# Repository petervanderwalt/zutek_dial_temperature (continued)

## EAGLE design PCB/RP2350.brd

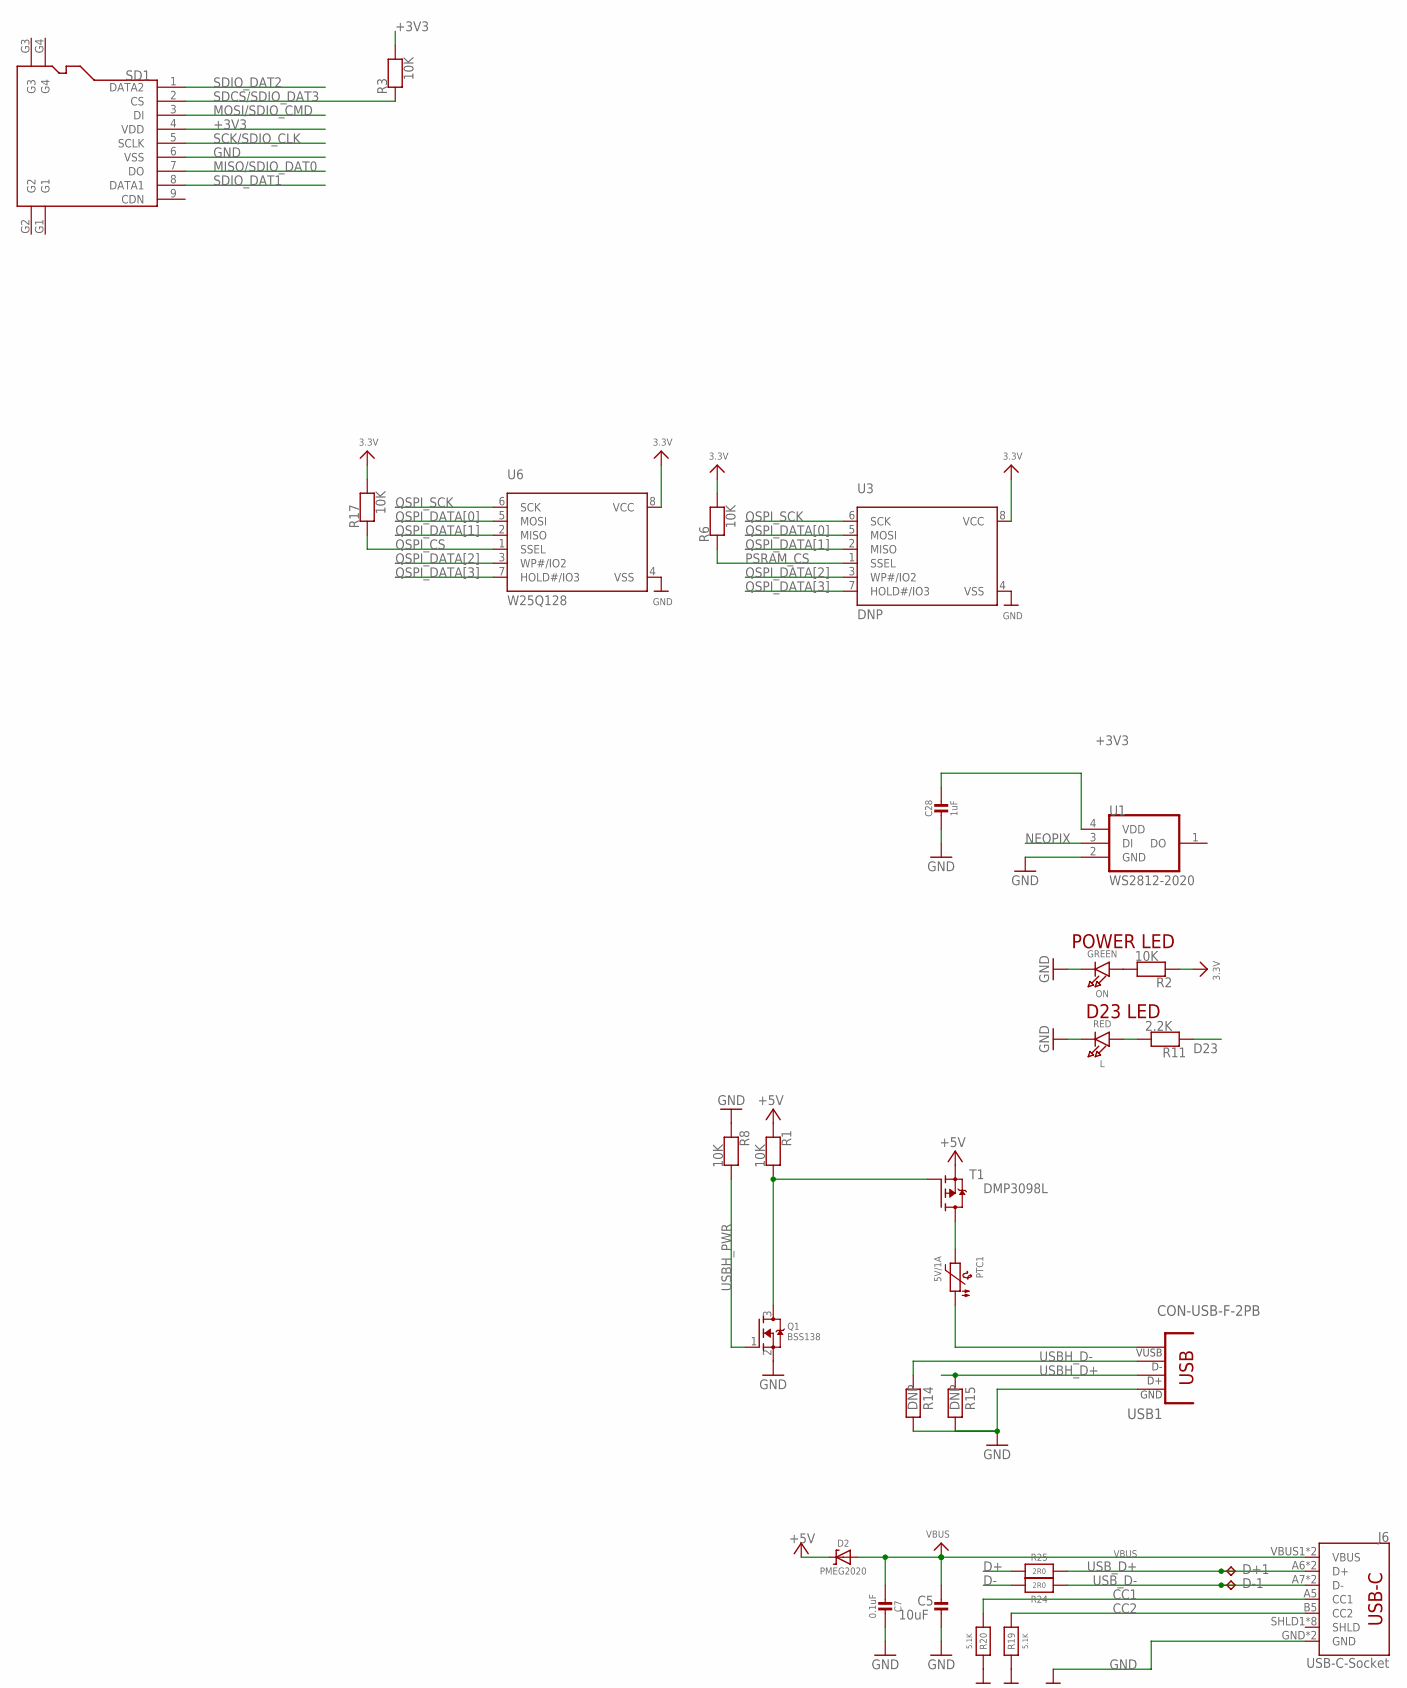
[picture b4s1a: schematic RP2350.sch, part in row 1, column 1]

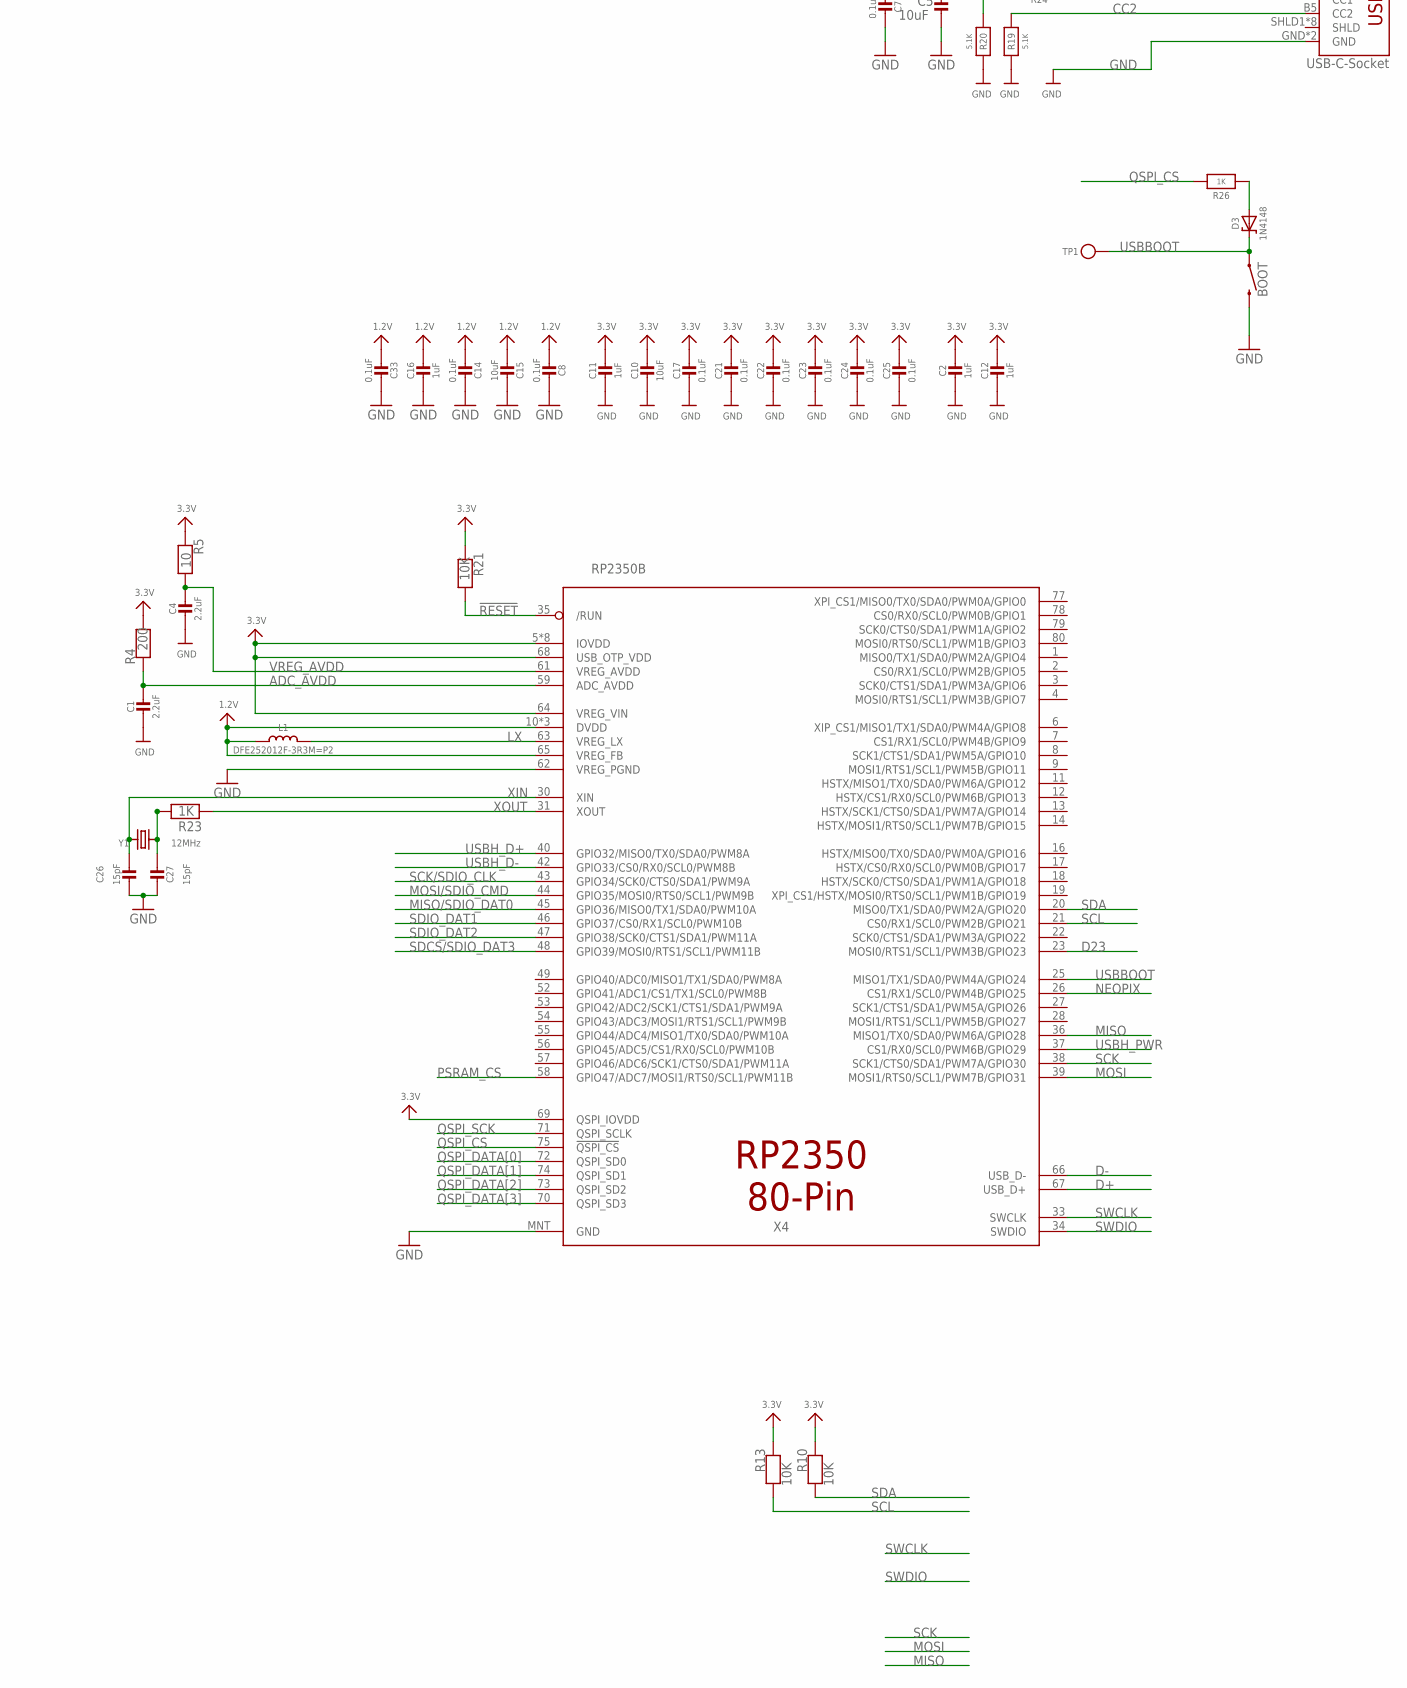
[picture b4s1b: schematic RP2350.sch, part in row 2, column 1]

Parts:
BOOT: MOMENTARY-SWITCH-SPST-SMD-6.0X3.5MM; TACTILE_SWITCH_SMD_6.0X3.5MM
C1, C4: 2.2uF; 0603-NO
C2, C11, C12, C16, C28: 1uF; 0603-NO
C5: 10uF; 0805-NO
C7, C8, C14, C17, C21, C22, C23, C24, C25, C33: 0.1uF; 0603-NO
C10, C15: 10uF; 0603-NO_WIDE
C26, C27: 15pF; 0603-NO
D2: PMEG2020; SOD-323
D3: 1N4148; SOD-323
D+1: TPB1,27; B1,27
D-1: TPB1,27; B1,27
J6: USB-C-Socket; USB-C-16P
L: RED; CHIPLED_0603_NOOUTLINE
L1: DFE252012F-3R3M=P2; INDUCTOR_1007
ON: GREEN; CHIPLED_0603_NOOUTLINE
PTC1: 5V/1A; 0805-NO
Q1: BSS138; SOT23-WIDE
R1, R2, R3, R6, R8, R10, R13, R17, R21: 10K; 0603-NO
R4: 200; 0603-NO
R5: 10; 0603-NO
R11: 2.2K; 0603-NO
R14, R15: DNP; 0603-NO
R19, R20: 5.1K; 0603-NO
R23, R26: 1K; 0603-NO
R24, R25: 2R0; 0603-NO
SD1: HOLDER-MICROSD-9P; 9P-SMD-W/-RING
T1: DMP3098L; SOT23-WIDE
TP1: TESTPOINTROUND1.5MMNO; TESTPOINT_ROUND_1.5MM_NO
U1: WS2812-2020; LED_WS2812-2020
U3: DNP; SOIC8_208MIL
U6: W25Q128; SOIC8_208MIL
USB1: CON-USB-F-2PB; CONN_USB_A_F
X4: RP2350B; QFN80
Y1: 12MHz; CRYSTAL_2.5X2

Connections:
1.2V: C8.2, C14.2, C15.2, C16.1, C33.2, L1.P$1 (1), X4.10 (DVDD), X4.32 (DVDD), X4.51 (DVDD), X4.65 (VREG_FB)
!RESET: R21.2, X4.35 (/RUN)
+3V3: C2.1, C10.1, C11.1, C12.1, C17.1, C21.1, C22.1, C23.1, C24.1, C25.1, C28.1, R2.1, R3.2, R4.2, R5.1, R6.2, R10.1, R13.1, R17.2, R21.1, SD1.4 (VDD), U1.4 (VDD), U3.8 (VCC), U6.8 (VCC), X4.5 (IOVDD), X4.15 (IOVDD), X4.24 (IOVDD), X4.29 (IOVDD), X4.41 (IOVDD), X4.50 (IOVDD), X4.60 (IOVDD), X4.64 (VREG_VIN), X4.68 (USB_OTP_VDD), X4.69 (QSPI_IOVDD), X4.76 (IOVDD)
+5V: D2.C, R1.1, T1.2 (S)
ADC_AVDD: C1.1, R4.1, X4.59 (ADC_AVDD)
CC1: J6.A5 (CC1), R20.2
CC2: J6.B5 (CC2), R19.2
D23: R11.1, X4.23 (MOSI0/RTS1/SCL1/PWM3B/GPIO23)
D+: R25.2, X4.67 (USB_D+)
D-: R24.2, X4.66 (USB_D-)
GND: BOOT.2, C1.2, C2.2, C4.2, C5.1, C7.2, C8.1, C10.2, C11.2, C12.2, C14.1, C15.1, C16.2, C17.2, C21.2, C22.2, C23.2, C24.2, C25.2, C26.1, C27.1, C28.2, C33.1, J6.GND, J6.GND2 (GND), L.C, ON.C, Q1.2 (S), R8.1, R14.1, R15.1, R19.1, R20.1, SD1.6 (VSS), U1.2 (GND), U3.4 (VSS), U6.4 (VSS), USB1.4 (GND), X4.62 (VREG_PGND), X4.MNT (GND)
LX: L1.P$2 (2), X4.63 (VREG_LX)
MISO: X4.36 (MISO1/TX0/SDA0/PWM6A/GPIO28)
MISO/SDIO_DAT0: SD1.7 (DO), X4.45 (GPIO36/MISO0/TX1/SDA0/PWM10A)
MOSI: X4.39 (MOSI1/RTS0/SCL1/PWM7B/GPIO31)
MOSI/SDIO_CMD: SD1.3 (DI), X4.44 (GPIO35/MOSI0/RTS0/SCL1/PWM9B)
unnamed: L.A, R11.2
unnamed: ON.A, R2.2
unnamed: PTC1.1, USB1.1 (VUSB)
unnamed: PTC1.2, T1.3 (D)
unnamed: Q1.3 (D), R1.2, T1.1 (G)
unnamed: D3.A, R26.2
unnamed: C27.2, R23.1, Y1.3 (2)
NEOPIX: U1.3 (DI), X4.26 (CS1/RX1/SCL0/PWM4B/GPIO25)
PSRAM_CS: R6.1, U3.1 (SSEL), X4.58 (GPIO47/ADC7/MOSI1/RTS0/SCL1/PWM11B)
QSPI_CS: R17.1, R26.1, U6.1 (SSEL), X4.75 (!QSPI_CS)
QSPI_DATA[0]: U3.5 (MOSI), U6.5 (MOSI), X4.72 (QSPI_SD0)
QSPI_DATA[1]: U3.2 (MISO), U6.2 (MISO), X4.74 (QSPI_SD1)
QSPI_DATA[2]: U3.3 (WP#/IO2), U6.3 (WP#/IO2), X4.73 (QSPI_SD2)
QSPI_DATA[3]: U3.7 (HOLD#/IO3), U6.7 (HOLD#/IO3), X4.70 (QSPI_SD3)
QSPI_SCK: U3.6 (SCK), U6.6 (SCK), X4.71 (QSPI_SCLK)
SCK: X4.38 (SCK1/CTS0/SDA1/PWM7A/GPIO30)
SCK/SDIO_CLK: SD1.5 (SCLK), X4.43 (GPIO34/SCK0/CTS0/SDA1/PWM9A)
SCL: R13.2, X4.21 (CS0/RX1/SCL0/PWM2B/GPIO21)
SDA: R10.2, X4.20 (MISO0/TX1/SDA0/PWM2A/GPIO20)
SDCS/SDIO_DAT3: R3.1, SD1.2 (CS), X4.48 (GPIO39/MOSI0/RTS1/SCL1/PWM11B)
SDIO_DAT1: SD1.8 (DATA1), X4.46 (GPIO37/CS0/RX1/SCL0/PWM10B)
SDIO_DAT2: SD1.1 (DATA2), X4.47 (GPIO38/SCK0/CTS1/SDA1/PWM11A)
SWCLK: X4.33 (SWCLK)
SWDIO: X4.34 (SWDIO)
USBBOOT: BOOT.1, D3.C, TP1.P$1, X4.25 (MISO1/TX1/SDA0/PWM4A/GPIO24)
USBH_D+: R15.2, USB1.3 (D+), X4.40 (GPIO32/MISO0/TX0/SDA0/PWM8A)
USBH_D-: R14.2, USB1.2 (D-), X4.42 (GPIO33/CS0/RX0/SCL0/PWM8B)
USBH_PWR: Q1.1 (G), R8.2, X4.37 (CS1/RX0/SCL0/PWM6B/GPIO29)
USB_D+: D+1.TP, J6.A6 (D+), J6.B6 (D+), R25.1
USB_D-: D-1.TP, J6.A7 (D-), J6.B7 (D-), R24.1
VBUS: C5.2, C7.1, D2.A, J6.VBUS1 (VBUS), J6.VBUS2 (VBUS)
VREG_AVDD: C4.1, R5.2, X4.61 (VREG_AVDD)
XIN: C26.2, X4.30 (XIN), Y1.1
XOUT: R23.2, X4.31 (XOUT)

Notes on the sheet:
POWER LED
D23 LED

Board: 2 copper layers, 62 parts (0 on the bottom side), 45 nets, no tracks yet.

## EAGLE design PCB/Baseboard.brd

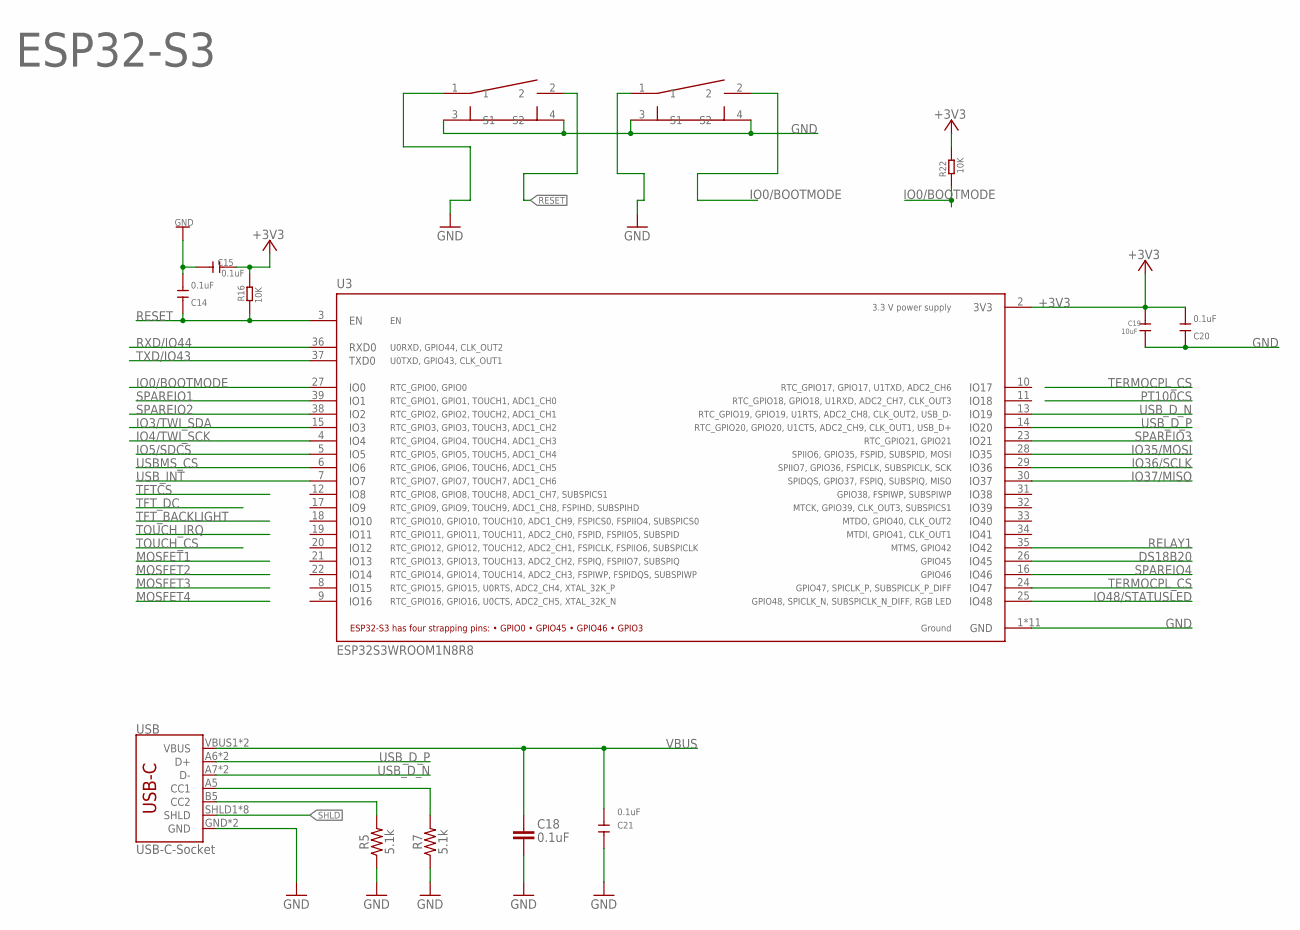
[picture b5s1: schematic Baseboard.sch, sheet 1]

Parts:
C14, C15, C20, C21: 0.1uF; DISCRETE_C0603
C18: 0.1uF; 0603-CAP
C19: 10uF; C1206
MODE: RIGHTANGLETACTILE; DP_DEVICES_SW_TACT_STANDARD_RIGHT_ANGLE
R5, R7: 5.1k; 0603@1
R16, R22: 10K; R0603
RESET: RIGHTANGLETACTILE; DP_DEVICES_SW_TACT_STANDARD_RIGHT_ANGLE
U3: ESP32S3WROOM1N8R8; XCVR_ESP32S3WROOM1N8R8
USB: USB-C-Socket; USB-C-16P

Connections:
+3V3: C15.1, C19.1, C20.2, R16.2, R22.2, U3.2 (3V3); also elsewhere on the board
CC1: R7.2, USB.A5 (CC1)
CC2: R5.2, USB.B5 (CC2)
DS18B20: U3.26 (IO45); also elsewhere on the board
GND: C14.2, C15.2, C18.2, C19.2, C20.1, C21.1, MODE.1, MODE.3 (S1), MODE.4 (S2), R5.1, R7.1, RESET.1, RESET.3 (S1), RESET.4 (S2), U3.1 (GND), U3.40 (GND), U3.41_1 (GND), U3.41_2 (GND), U3.41_3 (GND), U3.41_4 (GND), U3.41_5 (GND), U3.41_6 (GND), U3.41_7 (GND), U3.41_8 (GND), U3.41_9 (GND), USB.GND, USB.GND2 (GND); also elsewhere on the board
IO0/BOOTMODE: MODE.2, R22.1, U3.27 (IO0)
IO3/TWI_SDA: U3.15 (IO3); also elsewhere on the board
IO4/TWI_SCK: U3.4 (IO4); also elsewhere on the board
IO5/SDCS: U3.5 (IO5); also elsewhere on the board
IO35/MOSI: U3.28 (IO35); also elsewhere on the board
IO36/SCLK: U3.29 (IO36); also elsewhere on the board
IO37/MISO: U3.30 (IO37); also elsewhere on the board
IO48/STATUSLED: U3.25 (IO48); also elsewhere on the board
RELAY1: U3.35 (IO42); also elsewhere on the board
RESET: C14.1, R16.1, RESET.2, U3.3 (EN)
RXD/IO44: U3.36 (RXD0); also elsewhere on the board
SHLD: USB.SHLD1 (SHLD), USB.SHLD2 (SHLD), USB.SHLD3 (SHLD), USB.SHLD4 (SHLD), USB.SHLD5 (SHLD), USB.SHLD6 (SHLD), USB.SHLD7 (SHLD), USB.SHLD8 (SHLD)
SPAREIO1: U3.39 (IO1); also elsewhere on the board
SPAREIO2: U3.38 (IO2); also elsewhere on the board
SPAREIO3: U3.23 (IO21); also elsewhere on the board
SPAREIO4: U3.16 (IO46); also elsewhere on the board
TERMOCPL_CS: U3.24 (IO47); also elsewhere on the board
TXD/IO43: U3.37 (TXD0); also elsewhere on the board
USBMS_CS: U3.6 (IO6); also elsewhere on the board
USB_D_N: U3.13 (IO19), USB.A7 (D-), USB.B7 (D-)
USB_D_P: U3.14 (IO20), USB.A6 (D+), USB.B6 (D+)
USB_INT: U3.7 (IO7); also elsewhere on the board
VBUS: C18.1, C21.2, USB.VBUS1 (VBUS), USB.VBUS2 (VBUS); also elsewhere on the board

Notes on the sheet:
ESP32-S3

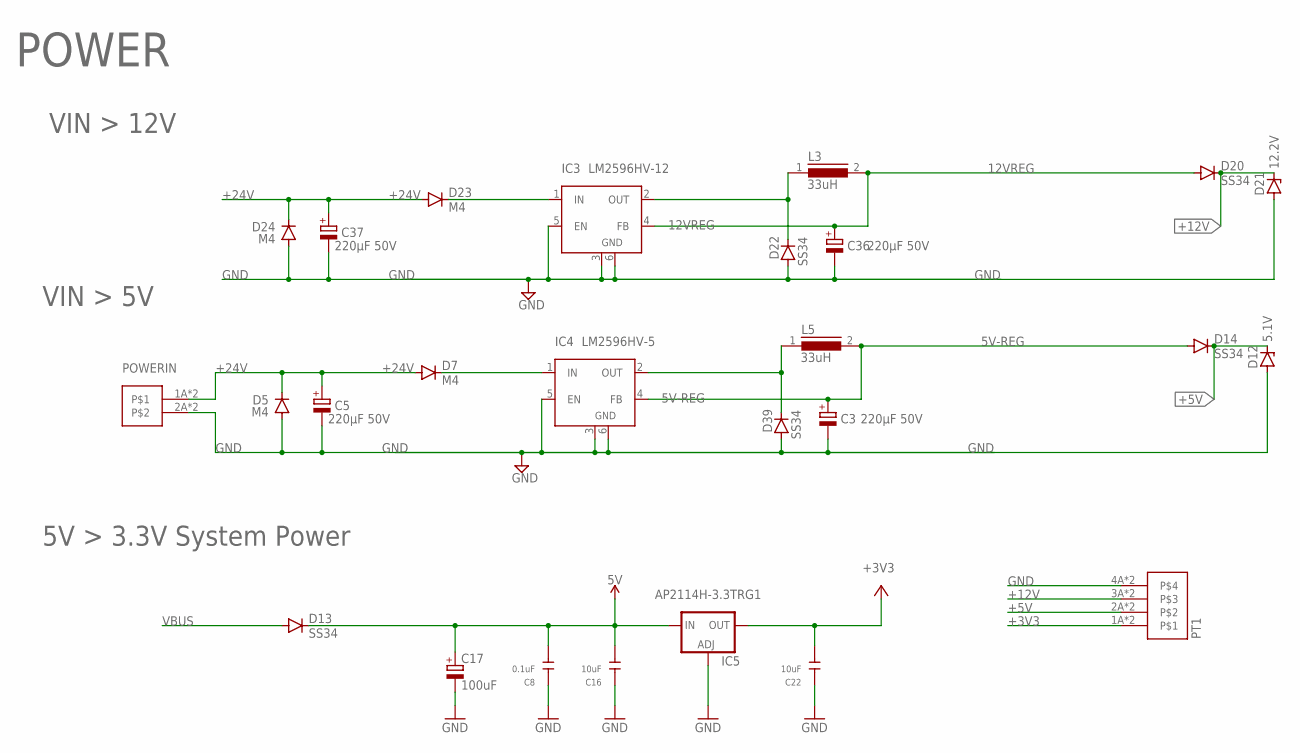
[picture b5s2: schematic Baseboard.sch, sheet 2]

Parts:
C3, C5, C36, C37: 220µF 50V; PANASONIC_E
C8: 0.1uF; DISCRETE_C0603
C16, C22: 10uF; C1206
C17: 100uF; PANASONIC_D
D5, D7, D23, D24: M4; DO-214AC
D12: 5.1V; SMB
D13, D14, D20: SS34; DO-214AC
D21: 12.2V; SMB
D22, D39: SS34; SOD87
IC3: LM2596HV-12; TO263-5
IC4: LM2596HV-5; TO263-5
IC5: AP2114H-3.3TRG1; SOT223
L3, L5: 33uH; DR127
POWERIN: WJ212R-THR-3.5-2
PT1: WJ212R-THR-3.5-4

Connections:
5V-REG: C3.+, D14.A, IC4.4 (FB), L5.2
12VREG: C36.+, D20.A, IC3.4 (FB), L3.2
+3V3: C22.1, IC5.4 (OUT), PT1.1A, PT1.1B; also elsewhere on the board
+5V: C8.2, C16.1, C17.+, D12.C, D13.C, D14.C, IC5.3 (IN), PT1.2A, PT1.2B; also elsewhere on the board
+12V: D20.C, D21.C, PT1.3A, PT1.3B
+24V: C5.+, C37.+, D5.C, D7.A, D23.A, D24.C, POWERIN.1A, POWERIN.1B; also elsewhere on the board
+24V1: D7.C, IC4.1 (IN)
+24V2: D23.C, IC3.1 (IN)
GND: C3.-, C5.-, C8.1, C16.2, C17.-, C22.2, C36.-, C37.-, D5.A, D12.A, D21.A, D22.2 (A), D24.A, D39.2 (A), IC3.3 (GND), IC3.5 (EN), IC3.6 (GND), IC4.3 (GND), IC4.5 (EN), IC4.6 (GND), IC5.1 (ADJ), POWERIN.2A, POWERIN.2B, PT1.4A, PT1.4B; also elsewhere on the board
unnamed: D22.1 (C), IC3.2 (OUT), L3.1
unnamed: D39.1 (C), IC4.2 (OUT), L5.1
VBUS: D13.A; also elsewhere on the board

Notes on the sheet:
5V > 3.3V System Power
POWER
VIN > 5V
VIN > 12V

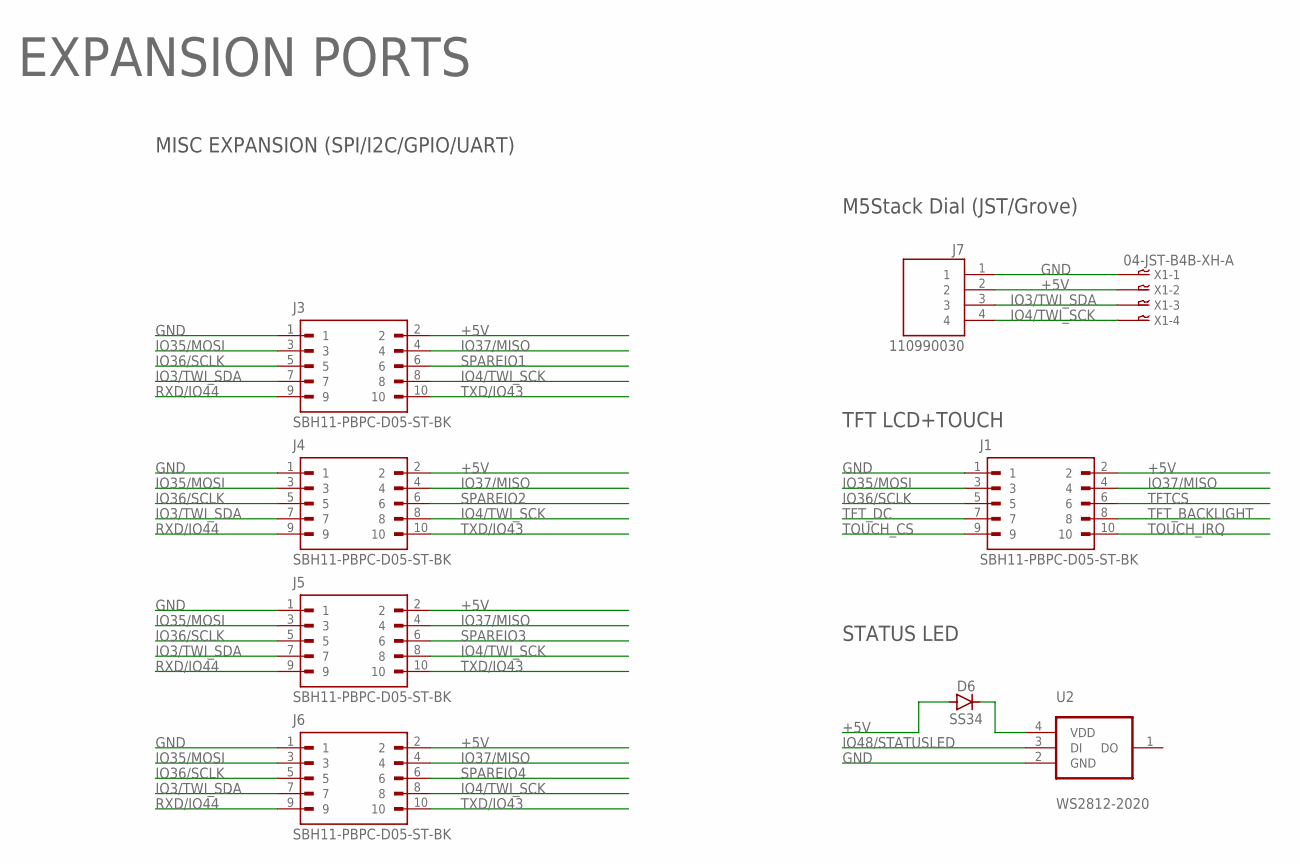
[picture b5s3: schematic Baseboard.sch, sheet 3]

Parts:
D6: SS34; SOD87
J1, J3, J4, J5, J6: SBH11-PBPC-D05-ST-BK; SULLINS_SBH11-PBPC-D05-ST-BK
J7: 110990030; SEEED_110990030
U2: WS2812-2020; LED_WS2812-2020
X1: 04-JST-B4B-XH-A; B4B-XH

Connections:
+5V: D6.2 (A), J1.2, J3.2, J4.2, J5.2, J6.2, J7.2, X1.P$2; also elsewhere on the board
GND: J1.1, J3.1, J4.1, J5.1, J6.1, J7.1, U2.2 (GND), X1.P$1; also elsewhere on the board
IO3/TWI_SDA: J3.7, J4.7, J5.7, J6.7, J7.3, X1.P$3; also elsewhere on the board
IO4/TWI_SCK: J3.8, J4.8, J5.8, J6.8, J7.4, X1.P$4; also elsewhere on the board
IO35/MOSI: J1.3, J3.3, J4.3, J5.3, J6.3; also elsewhere on the board
IO36/SCLK: J1.5, J3.5, J4.5, J5.5, J6.5; also elsewhere on the board
IO37/MISO: J1.4, J3.4, J4.4, J5.4, J6.4; also elsewhere on the board
IO48/STATUSLED: U2.3 (DI); also elsewhere on the board
unnamed: D6.1 (C), U2.4 (VDD)
RXD/IO44: J3.9, J4.9, J5.9, J6.9; also elsewhere on the board
SPAREIO1: J3.6; also elsewhere on the board
SPAREIO2: J4.6; also elsewhere on the board
SPAREIO3: J5.6; also elsewhere on the board
SPAREIO4: J6.6; also elsewhere on the board
TFTCS: J1.6
TFT_BACKLIGHT: J1.8
TFT_DC: J1.7
TOUCH_CS: J1.9
TOUCH_IRQ: J1.10
TXD/IO43: J3.10, J4.10, J5.10, J6.10; also elsewhere on the board

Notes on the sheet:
M5Stack Dial (JST/Grove)
TFT LCD+TOUCH
MISC EXPANSION (SPI/I2C/GPIO/UART)
EXPANSION PORTS
STATUS LED

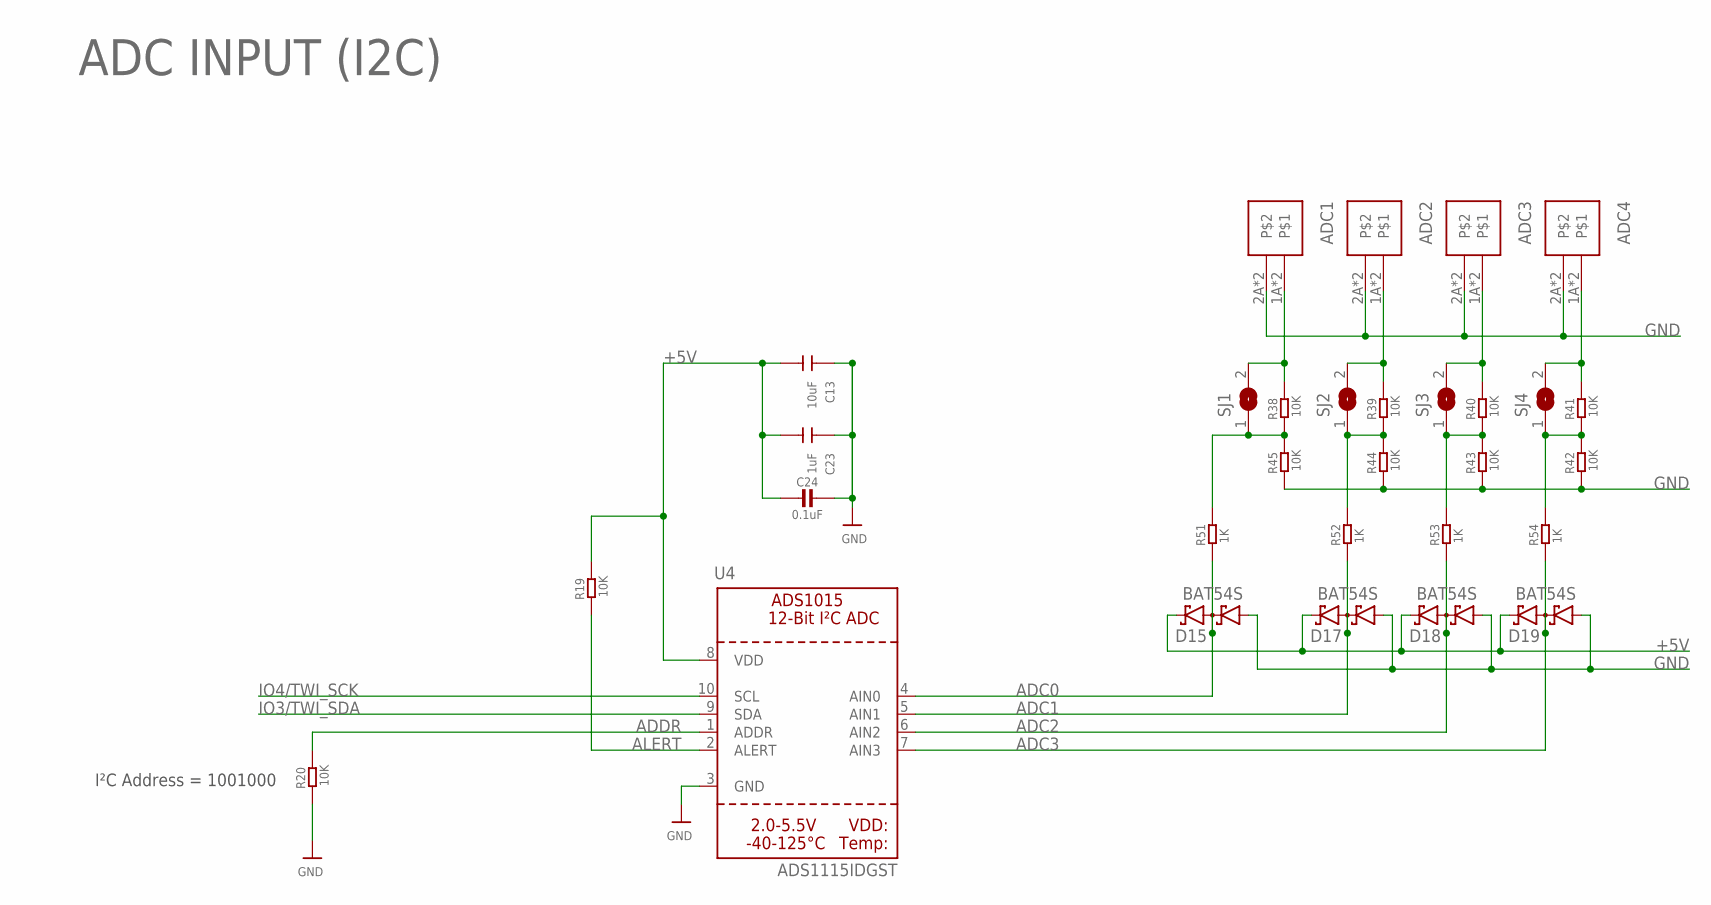
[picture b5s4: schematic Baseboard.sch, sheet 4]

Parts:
ADC1, ADC2, ADC3, ADC4: WJ212R-THR-3.5-2
C13: 10uF; C1206
C23: 1uF; C1206
C24: 0.1uF; 0805-NO
D15, D17, D18, D19: BAT54S; SOT23
R19, R20: 10K; R0603
R38, R39, R40, R41, R42, R43, R44, R45: 10K; R0204/5
R51, R52, R53, R54: 1K; R0204/5
SJ1, SJ2, SJ3, SJ4: SJ
U4: ADS1115IDGST; MSOP10

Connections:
+5V: C13.1, C23.1, C24.2, D15.2 (C2), D17.2 (C2), D18.2 (C2), D19.2 (C2), R19.1, U4.8 (VDD); also elsewhere on the board
ADC0: D15.3 (C1A2), R51.2, U4.4 (AIN0)
ADC1: D17.3 (C1A2), R52.2, U4.5 (AIN1)
ADC2: D18.3 (C1A2), R53.2, U4.6 (AIN2)
ADC3: D19.3 (C1A2), R54.2, U4.7 (AIN3)
ADDR: R20.1, U4.1 (ADDR); also elsewhere on the board
ALERT: R19.2, U4.2 (ALERT); also elsewhere on the board
GND: ADC1.2A, ADC1.2B, ADC2.2A, ADC2.2B, ADC3.2A, ADC3.2B, ADC4.2A, ADC4.2B, C13.2, C23.2, C24.1, D15.1 (A1), D17.1 (A1), D18.1 (A1), D19.1 (A1), R20.2, R42.2, R43.2, R44.2, R45.2, U4.3 (GND); also elsewhere on the board
IO3/TWI_SDA: U4.9 (SDA); also elsewhere on the board
IO4/TWI_SCK: U4.10 (SCL); also elsewhere on the board
unnamed: ADC1.1A, ADC1.1B, R38.1, SJ1.2
unnamed: ADC2.1A, ADC2.1B, R39.1, SJ2.2
unnamed: ADC3.1A, ADC3.1B, R40.1, SJ3.2
unnamed: ADC4.1A, ADC4.1B, R41.1, SJ4.2
unnamed: R38.2, R45.1, R51.1, SJ1.1
unnamed: R39.2, R44.1, R52.1, SJ2.1
unnamed: R40.2, R43.1, R53.1, SJ3.1
unnamed: R41.2, R42.1, R54.1, SJ4.1

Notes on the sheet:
I²C Address = 1001000
ADC INPUT (I2C)

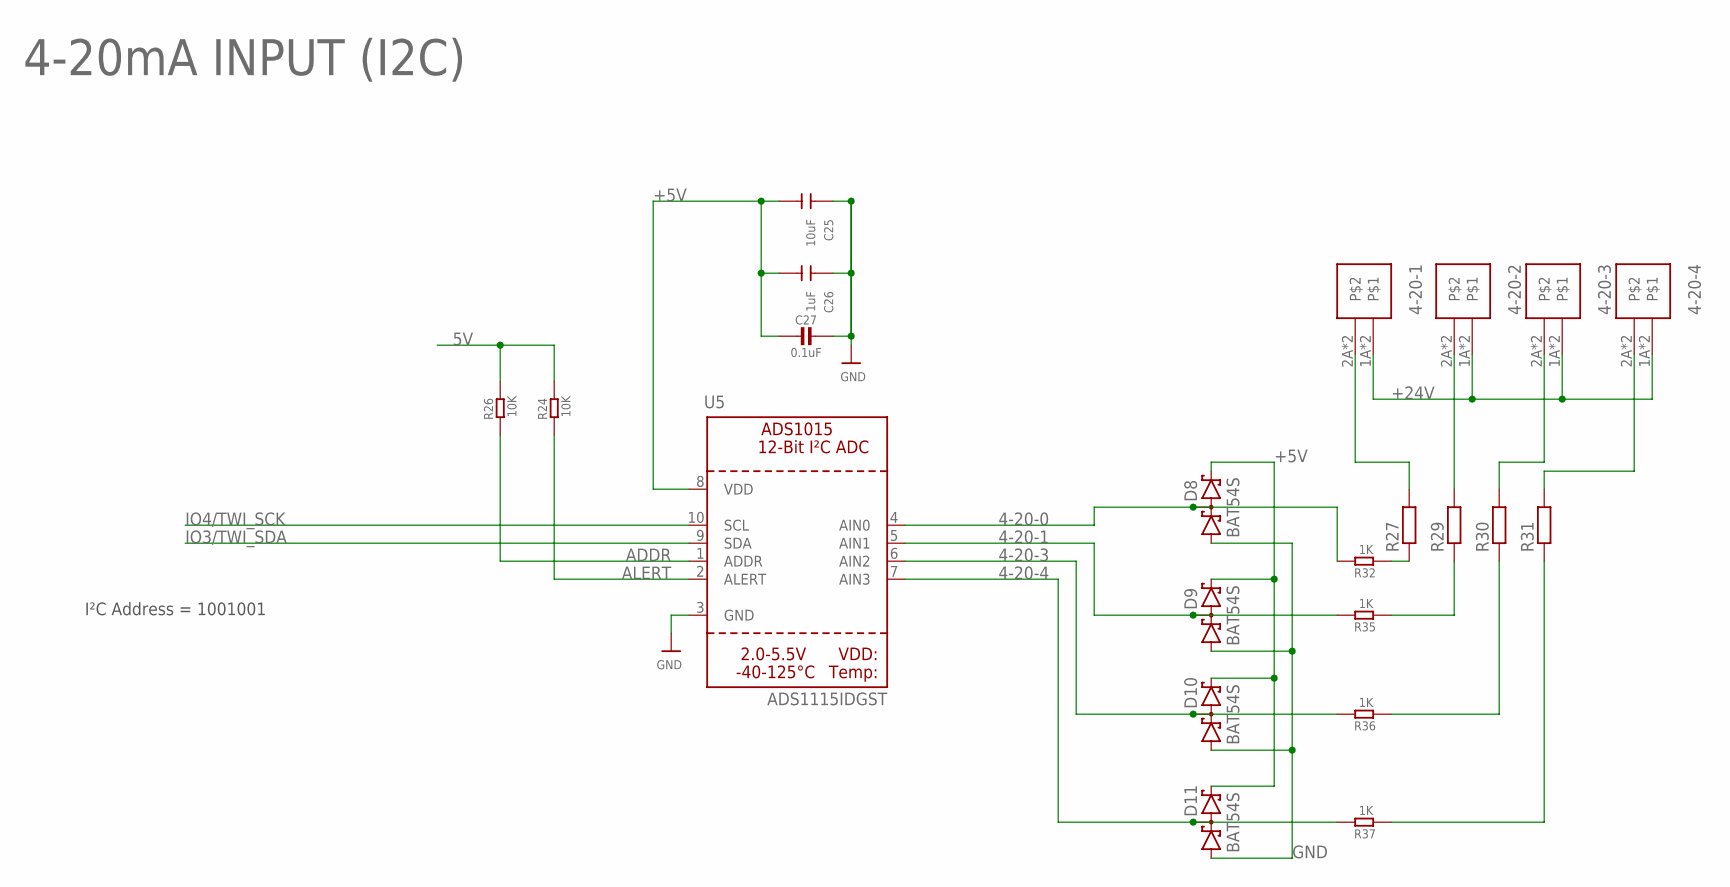
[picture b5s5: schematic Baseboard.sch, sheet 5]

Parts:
4-20-1, 4-20-2, 4-20-3, 4-20-4: WJ212R-THR-3.5-2
C25: 10uF; C1206
C26: 1uF; C1206
C27: 0.1uF; 0805-NO
D8, D9, D10, D11: BAT54S; SOT23
R24, R26: 10K; R0603
R27, R29, R30, R31: R-EU_R2512; R2512
R32, R35, R36, R37: 1K; R0603
U5: ADS1115IDGST; MSOP10

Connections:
4-20-0: D8.3 (C1A2), R32.1, U5.4 (AIN0)
4-20-1: D9.3 (C1A2), R35.1, U5.5 (AIN1)
4-20-3: D10.3 (C1A2), R36.1, U5.6 (AIN2)
4-20-4: D11.3 (C1A2), R37.1, U5.7 (AIN3)
5V: R24.1, R26.1; also elsewhere on the board
+5V: C25.1, C26.1, C27.2, D8.2 (C2), D9.2 (C2), D10.2 (C2), D11.2 (C2), U5.8 (VDD); also elsewhere on the board
+24V: 4-20-1.1A, 4-20-1.1B, 4-20-2.1A, 4-20-2.1B, 4-20-3.1A, 4-20-3.1B, 4-20-4.1A, 4-20-4.1B; also elsewhere on the board
ADDR: R26.2, U5.1 (ADDR); also elsewhere on the board
ALERT: R24.2, U5.2 (ALERT); also elsewhere on the board
GND: C25.2, C26.2, C27.1, D8.1 (A1), D9.1 (A1), D10.1 (A1), D11.1 (A1), U5.3 (GND); also elsewhere on the board
IO3/TWI_SDA: U5.9 (SDA); also elsewhere on the board
IO4/TWI_SCK: U5.10 (SCL); also elsewhere on the board
unnamed: R31.1, R37.2
unnamed: R30.1, R36.2
unnamed: R29.1, R35.2
unnamed: R27.1, R32.2
unnamed: 4-20-1.2A, 4-20-1.2B, R27.2
unnamed: 4-20-2.2A, 4-20-2.2B, R29.2
unnamed: 4-20-3.2A, 4-20-3.2B, R30.2
unnamed: 4-20-4.2A, 4-20-4.2B, R31.2

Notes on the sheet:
I²C Address = 1001001
4-20mA INPUT (I2C)

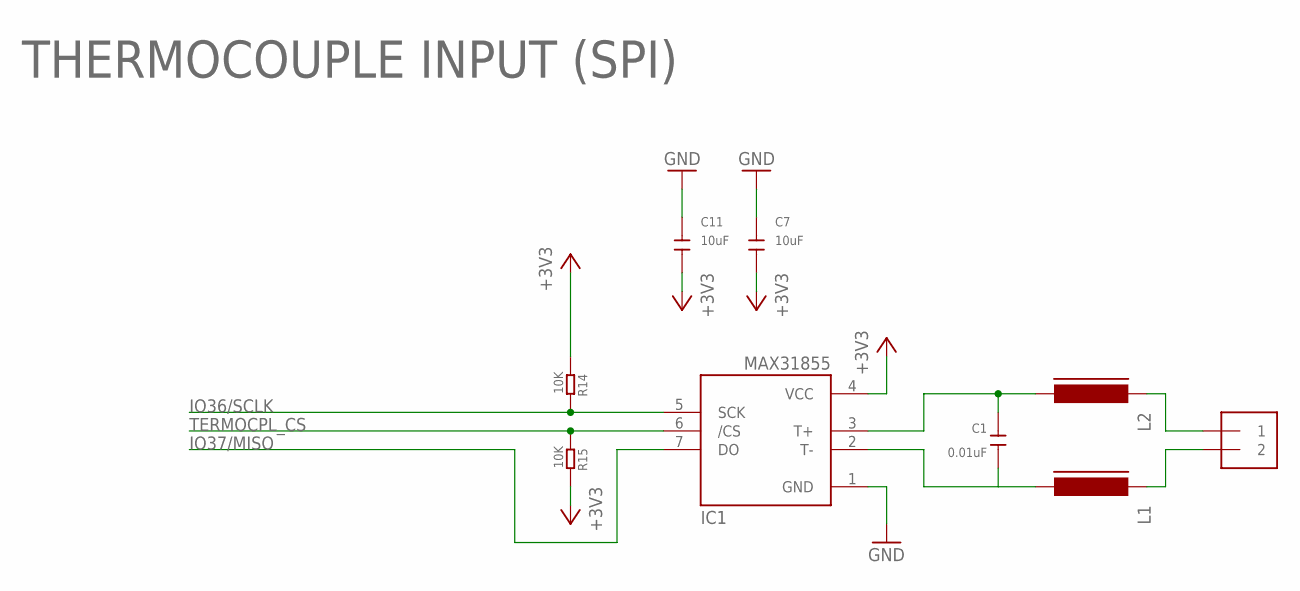
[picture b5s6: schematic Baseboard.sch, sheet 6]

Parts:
C1: 0.01uF; DISCRETE_C0603
C7, C11: 10uF; C1206
IC1: MAX31855; SO08
J9: 1X2-3.5MM
L1, L2: FERRITE-0805; FB805
R14, R15: 10K; R0603

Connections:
+3V3: C7.1, C11.1, IC1.4 (VCC), R14.1, R15.2; also elsewhere on the board
GND: C7.2, C11.2, IC1.1 (GND); also elsewhere on the board
IO36/SCLK: IC1.5 (SCK), R14.2; also elsewhere on the board
IO37/MISO: IC1.7 (DO); also elsewhere on the board
unnamed: J9.2, L1.1
unnamed: C1.2, IC1.2 (T-), L1.2
unnamed: J9.1, L2.1
unnamed: C1.1, IC1.3 (T+), L2.2
TERMOCPL_CS: IC1.6 (/CS), R15.1; also elsewhere on the board

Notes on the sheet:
THERMOCOUPLE INPUT (SPI)

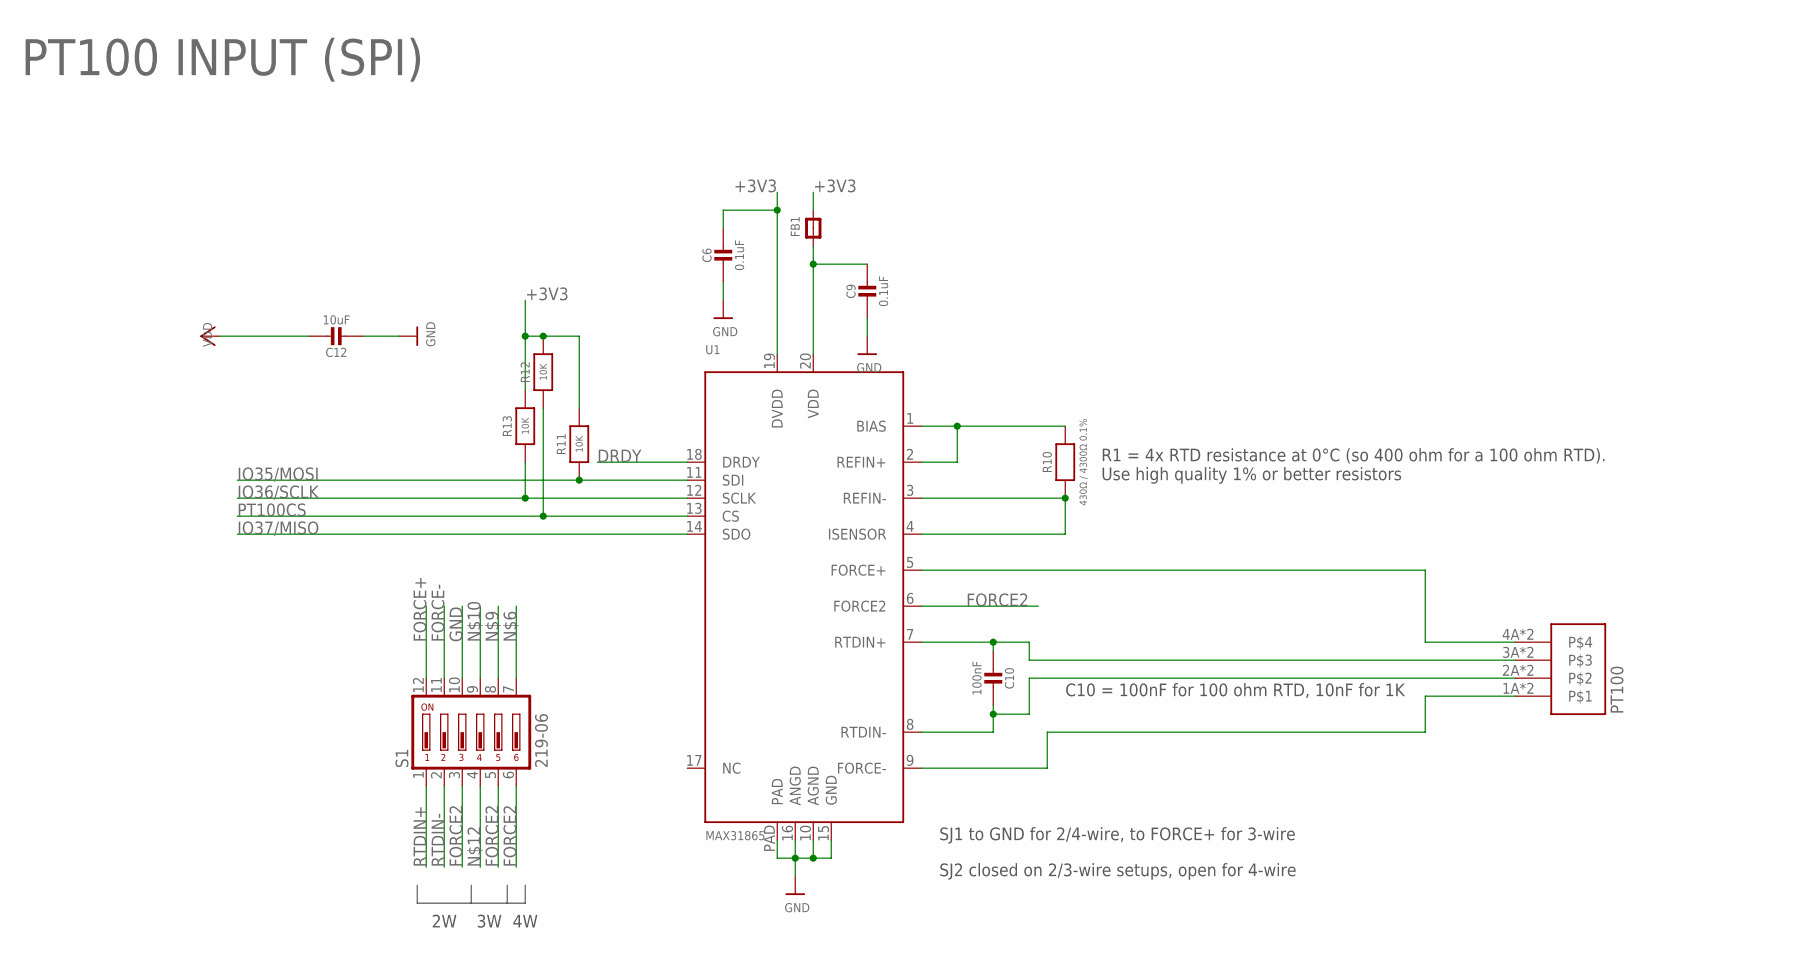
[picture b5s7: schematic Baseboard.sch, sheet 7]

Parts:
C6, C9: 0.1uF; 0805-NO
C10: 100nF; 0805-NO
C12: 10uF; 0805-NO
FB1: FERRITE-0805NO; 0805-NO
PT100: WJ212R-THR-3.5-4
R10: 430Ω / 4300Ω 0.1%; 0805-NO
R11, R12, R13: 10K; 0805-NO
S1: 219-06; CTS-219-06
U1: MAX31865; QFN20_4MM_0.65MM

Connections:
+3V3: C6.1, C12.1, FB1.2, R11.2, R12.2, R13.2, U1.19 (DVDD); also elsewhere on the board
DRDY: U1.18 (DRDY)
FORCE2: S1.3, S1.5, S1.6, U1.6 (FORCE2)
FORCE+: PT100.4A, PT100.4B, S1.12, U1.5 (FORCE+)
FORCE-: PT100.1A, PT100.1B, S1.11, U1.9 (FORCE-)
GND: C6.2, C9.2, C12.2, S1.10, U1.10 (AGND), U1.15 (GND), U1.16 (ANGD), U1.PAD; also elsewhere on the board
IO35/MOSI: R11.1, U1.11 (SDI); also elsewhere on the board
IO36/SCLK: R13.1, U1.12 (SCLK); also elsewhere on the board
IO37/MISO: U1.14 (SDO); also elsewhere on the board
unnamed: R10.2, U1.1 (BIAS), U1.2 (REFIN+)
unnamed: R10.1, U1.3 (REFIN-), U1.4 (ISENSOR)
unnamed: C9.1, FB1.1, U1.20 (VDD)
PT100CS: R12.1, U1.13 (CS)
RTDIN+: C10.1, PT100.3A, PT100.3B, S1.1, U1.7 (RTDIN+)
RTDIN-: C10.2, PT100.2A, PT100.2B, S1.2, U1.8 (RTDIN-)

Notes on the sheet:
C10 = 100nF for 100 ohm RTD, 10nF for 1K
R1 = 4x RTD resistance at 0°C (so 400 ohm for a 100 ohm RTD). Use high quality 1% or better resistors
SJ1 to GND for 2/4-wire, to FORCE+ for 3-wire
SJ2 closed on 2/3-wire setups, open for 4-wire
PT100 INPUT (SPI)
